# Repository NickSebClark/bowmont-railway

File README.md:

Source code and designs for my model railway.

### Contents

[arduino-command](arduino-command/) | 
Central controller with servo shield. Connects to PC and arduino-remote.

[arduino-remote](arduino-remote/) | Handheld remote to control the points.

[pc-control](pc-control/) | Python app to control the points on PC.

[anyrail](anyrail/) | Track plan.

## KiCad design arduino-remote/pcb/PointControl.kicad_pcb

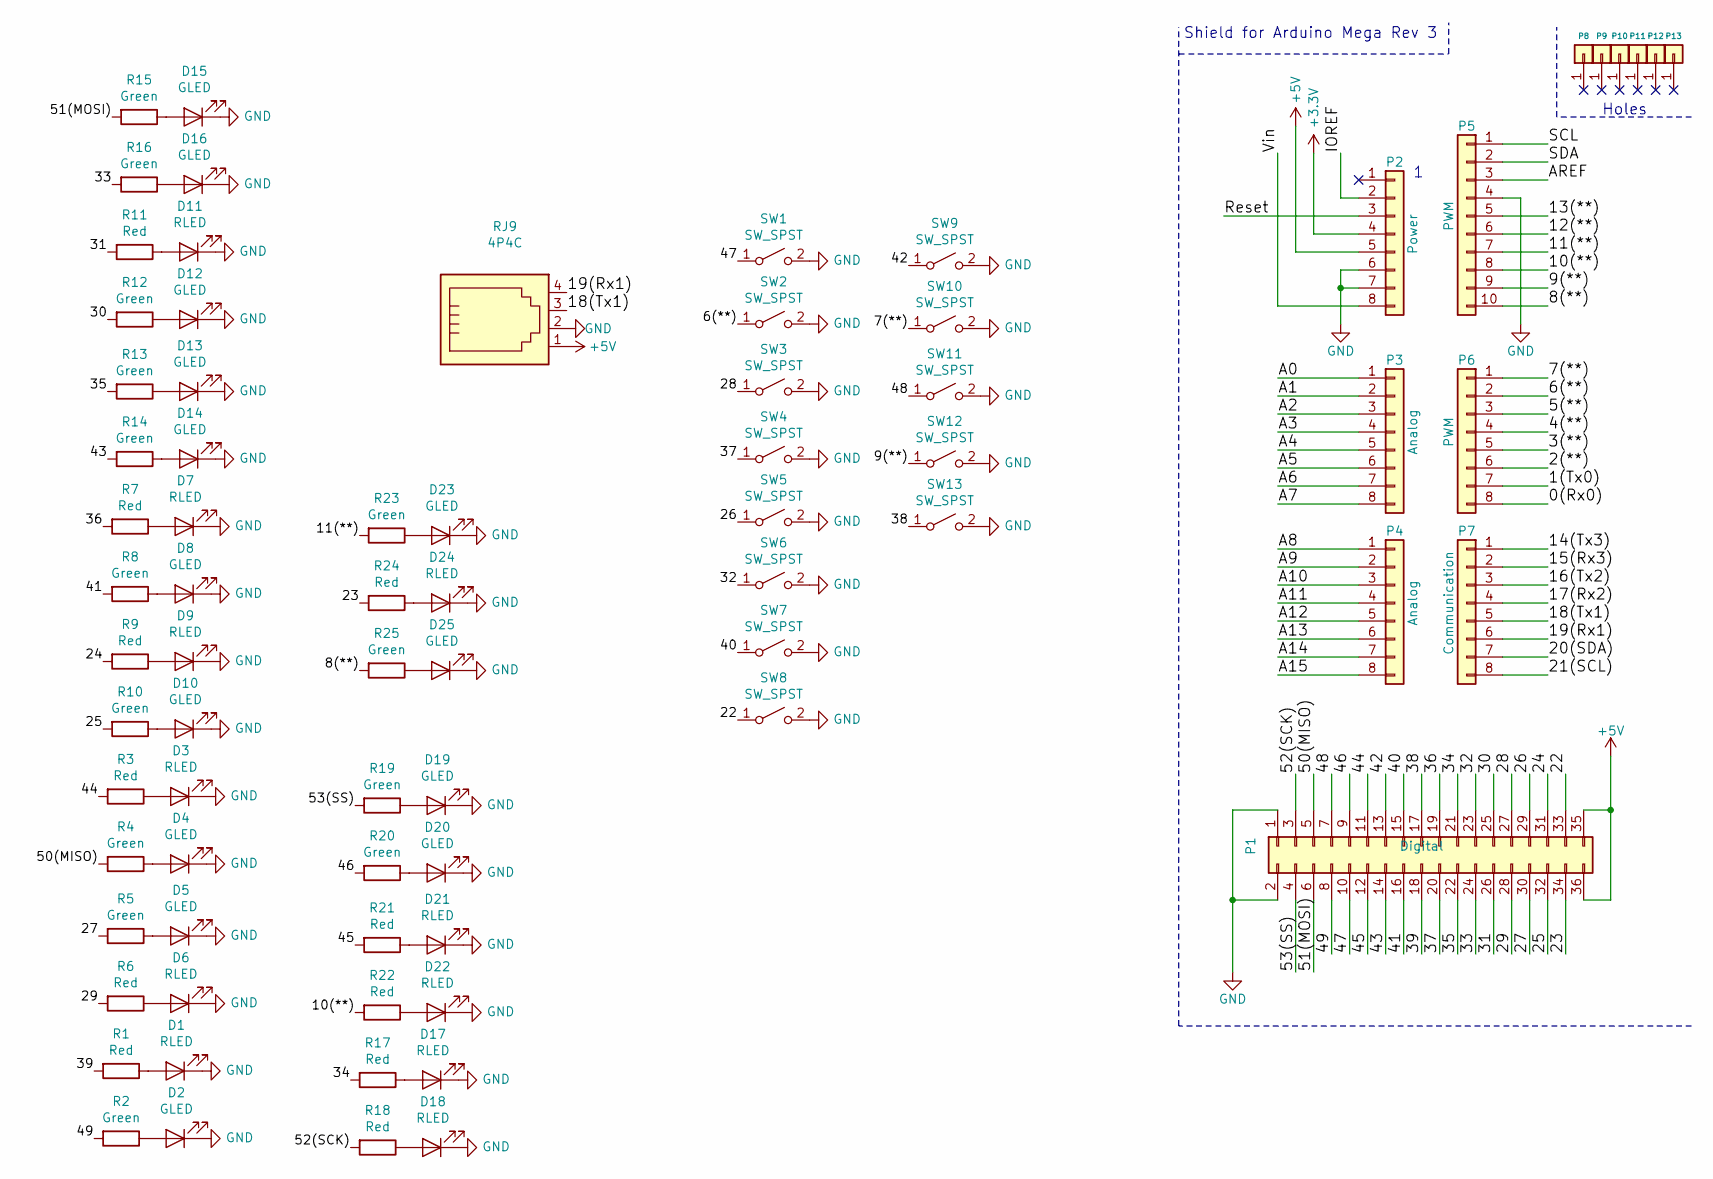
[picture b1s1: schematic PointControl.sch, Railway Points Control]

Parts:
D1, D3, D6, D7, D9, D11, D17, D18, D21, D22, D24: RLED; LED_0805_HandSoldering
D2, D4, D5, D8, D10, D12, D13, D14, D15, D16, D19, D20, D23, D25: GLED; LED_0805_HandSoldering
P1: Digital; Socket_Strip_Arduino_2x18
P2: Power; Socket_Strip_Arduino_1x08
P3, P4: Analog; Socket_Strip_Arduino_1x08
P5: PWM; Socket_Strip_Arduino_1x10
P6: PWM; Socket_Strip_Arduino_1x08
P7: Communication; Socket_Strip_Arduino_1x08
P8, P9, P10, P11, P12, P13: CONN_01X01; Arduino_1pin
R1, R3, R6, R7, R9, R11, R17, R18, R21, R22, R24: Red; R_0805_HandSoldering
R2, R4, R5, R8, R10, R12, R13, R14, R15, R16, R19, R20, R23, R25: Green; R_0805_HandSoldering
RJ9: 4P4C; MHRJJ44NFRA
SW1, SW2, SW3, SW4, SW5, SW6, SW7, SW8, SW9, SW10, SW11, SW12, SW13: SW_SPST; SW_PUSH_6mm

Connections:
+3V3: P2.4
+5V: P1.35, P1.36, P2.5, RJ9.1
/0(Rx0): P6.8
/1(Tx0): P6.7
/2(**): P6.6
/3(**): P6.5
/4(**): P6.4
/5(**): P6.3
/6(**): P6.2, SW2.1 (A)
/7(**): P6.1, SW10.1 (A)
/8(**): P5.10, R25.2
/9(**): P5.9, SW12.1 (A)
/10(**): P5.8, R22.2
/11(**): P5.7, R23.2
/12(**): P5.6
/13(**): P5.5
/14(Tx3): P7.1
/15(Rx3): P7.2
/16(Tx2): P7.3
/17(Rx2): P7.4
/18(Tx1): P7.5, RJ9.3
/19(Rx1): P7.6, RJ9.4
/20(SDA): P7.7
/21(SCL): P7.8
/22: P1.33, SW8.1 (A)
/23: P1.34, R24.2
/24: P1.31, R9.2
/25: P1.32, R10.2
/26: P1.29, SW5.1 (A)
/27: P1.30, R5.2
/28: P1.27, SW3.1 (A)
/29: P1.28, R6.2
/30: P1.25, R12.2
/31: P1.26, R11.2
/32: P1.23, SW6.1 (A)
/33: P1.24, R16.2
/34: P1.21, R17.2
/35: P1.22, R13.2
/36: P1.19, R7.2
/37: P1.20, SW4.1 (A)
/38: P1.17, SW13.1 (A)
/39: P1.18, R1.2
/40: P1.15, SW7.1 (A)
/41: P1.16, R8.2
/42: P1.13, SW9.1 (A)
/43: P1.14, R14.2
/44: P1.11, R3.2
/45: P1.12, R21.2
/46: P1.9, R20.2
/47: P1.10, SW1.1 (A)
/48: P1.7, SW11.1 (A)
/49: P1.8, R2.2
/50(MISO): P1.5, R4.2
/51(MOSI): P1.6, R15.2
/52(SCK): P1.3, R18.2
/53(SS): P1.4, R19.2
/A0: P3.1
/A1: P3.2
/A2: P3.3
/A3: P3.4
/A4: P3.5
/A5: P3.6
/A6: P3.7
/A7: P3.8
/A8: P4.1
/A9: P4.2
/A10: P4.3
/A11: P4.4
/A12: P4.5
/A13: P4.6
/A14: P4.7
/A15: P4.8
/AREF: P5.3
/IOREF: P2.2
/Reset: P2.3
/SCL: P5.1
/SDA: P5.2
/Vin: P2.8
GND: D1.1 (K), D2.1 (K), D3.1 (K), D4.1 (K), D5.1 (K), D6.1 (K), D7.1 (K), D8.1 (K), D9.1 (K), D10.1 (K), D11.1 (K), D12.1 (K), D13.1 (K), D14.1 (K), D15.1 (K), D16.1 (K), D17.1 (K), D18.1 (K), D19.1 (K), D20.1 (K), D21.1 (K), D22.1 (K), D23.1 (K), D24.1 (K), D25.1 (K), P1.1, P1.2, P2.6, P2.7, P5.4, RJ9.2, SW1.2 (B), SW2.2 (B), SW3.2 (B), SW4.2 (B), SW5.2 (B), SW6.2 (B), SW7.2 (B), SW8.2 (B), SW9.2 (B), SW10.2 (B), SW11.2 (B), SW12.2 (B), SW13.2 (B)
unnamed: D1.2 (A), R1.1
unnamed: D2.2 (A), R2.1
unnamed: D3.2 (A), R3.1
unnamed: D4.2 (A), R4.1
unnamed: D5.2 (A), R5.1
unnamed: D6.2 (A), R6.1
unnamed: D7.2 (A), R7.1
unnamed: D8.2 (A), R8.1
unnamed: D9.2 (A), R9.1
unnamed: D10.2 (A), R10.1
unnamed: D11.2 (A), R11.1
unnamed: D12.2 (A), R12.1
unnamed: D13.2 (A), R13.1
unnamed: D14.2 (A), R14.1
unnamed: D15.2 (A), R15.1
unnamed: D16.2 (A), R16.1
unnamed: D17.2 (A), R17.1
unnamed: D18.2 (A), R18.1
unnamed: D19.2 (A), R19.1
unnamed: D20.2 (A), R20.1
unnamed: D21.2 (A), R21.1
unnamed: D22.2 (A), R22.1
unnamed: D23.2 (A), R23.1
unnamed: D24.2 (A), R24.1
unnamed: D25.2 (A), R25.1

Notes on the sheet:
Shield for Arduino Mega Rev 3
Holes

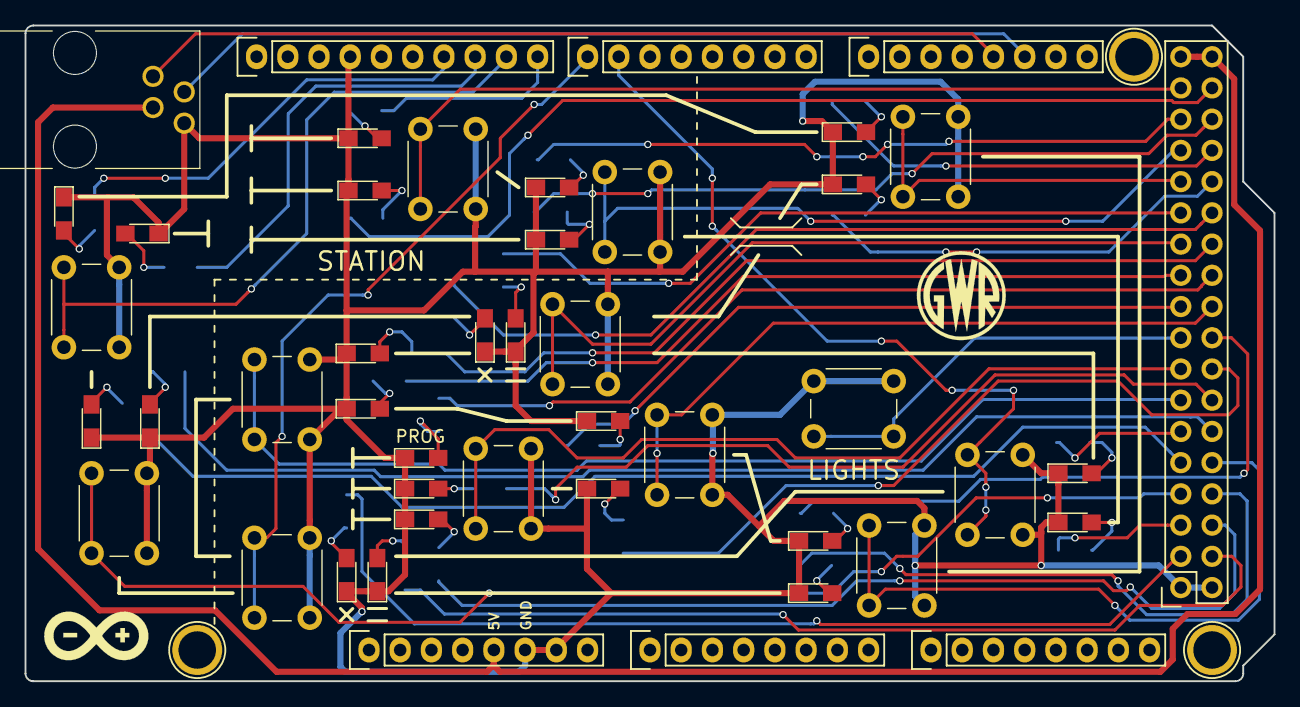
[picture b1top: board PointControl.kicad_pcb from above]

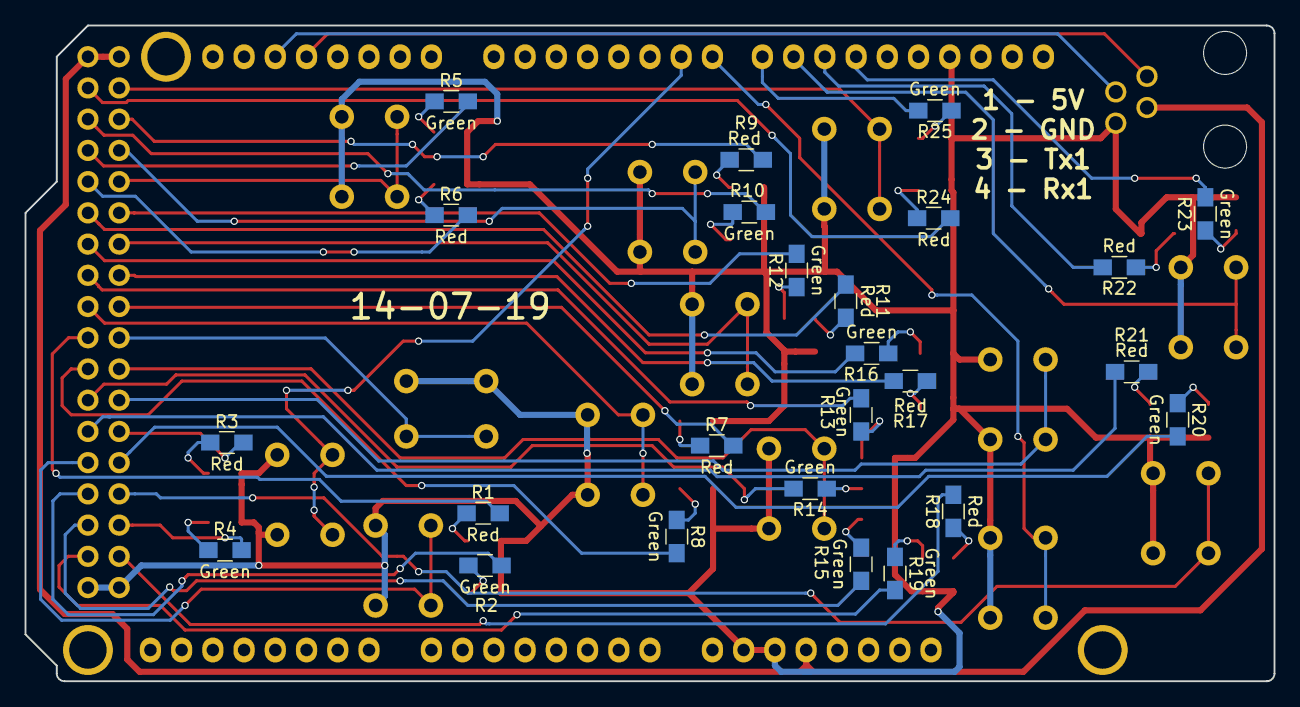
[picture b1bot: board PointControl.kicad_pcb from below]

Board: 2 copper layers, 101.6 x 53.3 mm, 74 parts (25 on the bottom side), 67 nets.

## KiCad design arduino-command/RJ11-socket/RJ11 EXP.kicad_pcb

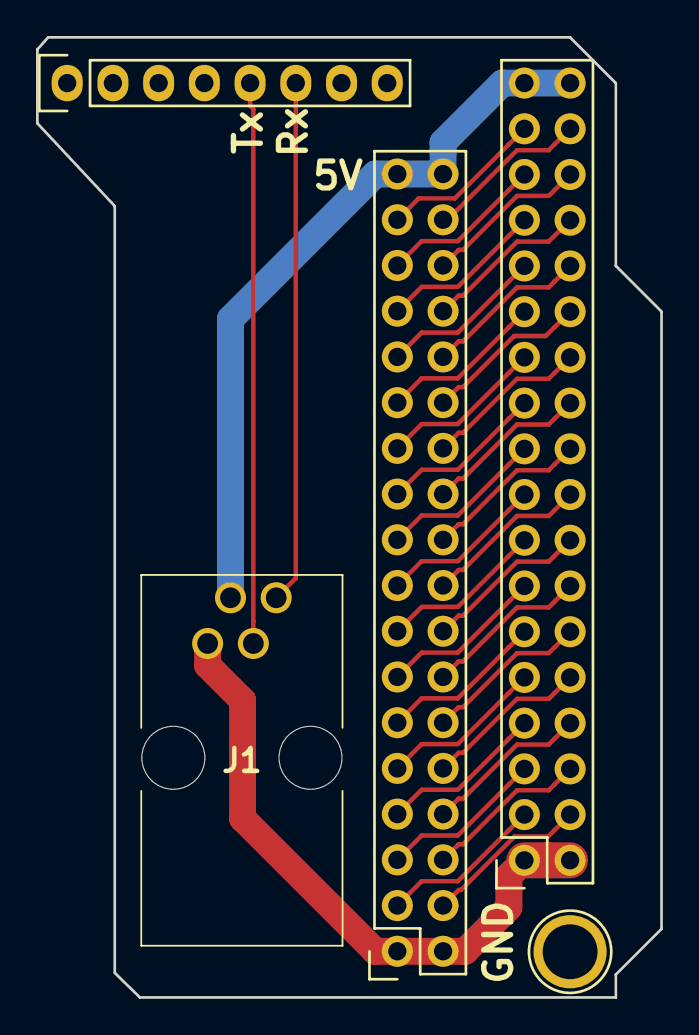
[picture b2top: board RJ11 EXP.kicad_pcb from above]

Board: 2 copper layers, 34.7 x 53.3 mm, 5 parts (0 on the bottom side), 36 nets.

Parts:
J1: RJ9; MHRJJ44NFRA
P1, P14: Digital; Socket_Strip_Arduino_2x18
P7: Communication; Socket_Strip_Arduino_1x08
P10: CONN_01X01; Arduino_1pin

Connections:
+5V: J1.4, P1.35, P1.36, P14.35, P14.36
/18(Tx1): J1.1, P7.5
/19(Rx1): J1.2, P7.6
/22: P1.33, P14.33
/23: P1.34, P14.34
/24: P1.31, P14.31
/25: P1.32, P14.32
/26: P1.29, P14.29
/27: P1.30, P14.30
/28: P1.27, P14.27
/29: P1.28, P14.28
/30: P1.25, P14.25
/31: P1.26, P14.26
/32: P1.23, P14.23
/33: P1.24, P14.24
/34: P1.21, P14.21
/35: P1.22, P14.22
/36: P1.19, P14.19
/37: P1.20, P14.20
/38: P1.17, P14.17
/39: P1.18, P14.18
/40: P1.15, P14.15
/41: P1.16, P14.16
/42: P1.13, P14.13
/43: P1.14, P14.14
/44: P1.11, P14.11
/45: P1.12, P14.12
/46: P1.9, P14.9
/47: P1.10, P14.10
/48: P1.7, P14.7
/49: P1.8, P14.8
/50(MISO): P1.5, P14.5
/51(MOSI): P1.6, P14.6
/52(SCK): P1.3, P14.3
/53(SS): P1.4, P14.4
GND: J1.3, P1.1, P1.2, P14.1, P14.2

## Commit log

2020-12-28 Beginning of main readme.
2022-03-25 Added Arduino Source
2022-03-29 First draft code ready for testing.
2023-01-04 Update README.md
    Changed the title formatting.
2023-04-26 Some old changes.
2023-04-26 Latest code.
    Changes from somewhere else on disk. This looks like the latest version.
2023-06-28 Update animate.py
    Hovering and clicking to move points around.
2023-06-30 Update animate.py
    Added basic point types.
    Added sections.
2023-06-30 Refactored into new filenames
2023-07-01 Vertical points and layout surface
2023-07-02 Refactored into layout. Added title.
2023-07-03 Added CrossOver point. Added settings.json
2023-07-05 Added signal
2023-07-05 Removed pyc files.
2023-07-05 Removed more pyc
2023-07-06 Docstrings and tidy title
2023-07-06 Added the font
2023-07-07 Added endstops to track sections
2023-07-07 Docstring for Track
2023-07-07 Moved to toml config. Layout size adjustment.
2023-07-07 Add GWR roundel. Refactor to connect points directly.
2023-07-08 Adjusted labels, size and added points.
2023-07-08 Added a load of track
2023-07-09 Add Triple Point, AA, Bridge, Track adjustments
2023-07-09 File renaming.
2023-07-09 Added a load of files
2023-07-10 Label positions, track fettling.
2023-07-10 Create LICENSE
2023-07-10 Added serial comms file. Updated settings toml
2023-07-11 Initial tries with serial comms.
2023-07-12 A bit of experimentation with serial.
2023-07-13 Added ZeroWaitSerial Class. Added serial monitor to main.
2023-07-24 Beginnings of serial decode.
2023-07-25 Parsing of serial synchronisation. Organisation of points to match PCB.
2023-07-26 Refactor serial_comms to be a child of serial. Added serial write on click.
2023-07-27 Added request sync button
2023-08-11 Remove flash lights
    Too much current draw.
2023-08-28 Added catch for no serial. Added rounded corners for track.
2023-08-29 Added Dummy Serial and Warning message
2023-08-29 Tidying up of the diagonal sections.
2023-08-29 Readme updates
2024-11-12 Add route highlighting on mouseover
2024-11-13 Added triple into route finding. Tidied up a bit.
2024-11-23 Got it working with UV
    Added the package thing. That was a bit complicated.
2024-12-15 Final changes for uv
2025-06-21 Servo settings
2025-07-07 rescaled ui
2025-07-13 Update arduino-command.ino
    servo values
2025-07-17 2x scaling
2025-07-17 quit when click top-right
2025-10-12 Some reliability improvements
2025-10-18 More servos.
    Update for triple.
2026-01-04 Added increment and decrement.
2026-01-17 points all dome!!!
2026-01-18 Servo tweaking
2026-01-18 More tweaks
2026-01-31 Got all the directions correct.
